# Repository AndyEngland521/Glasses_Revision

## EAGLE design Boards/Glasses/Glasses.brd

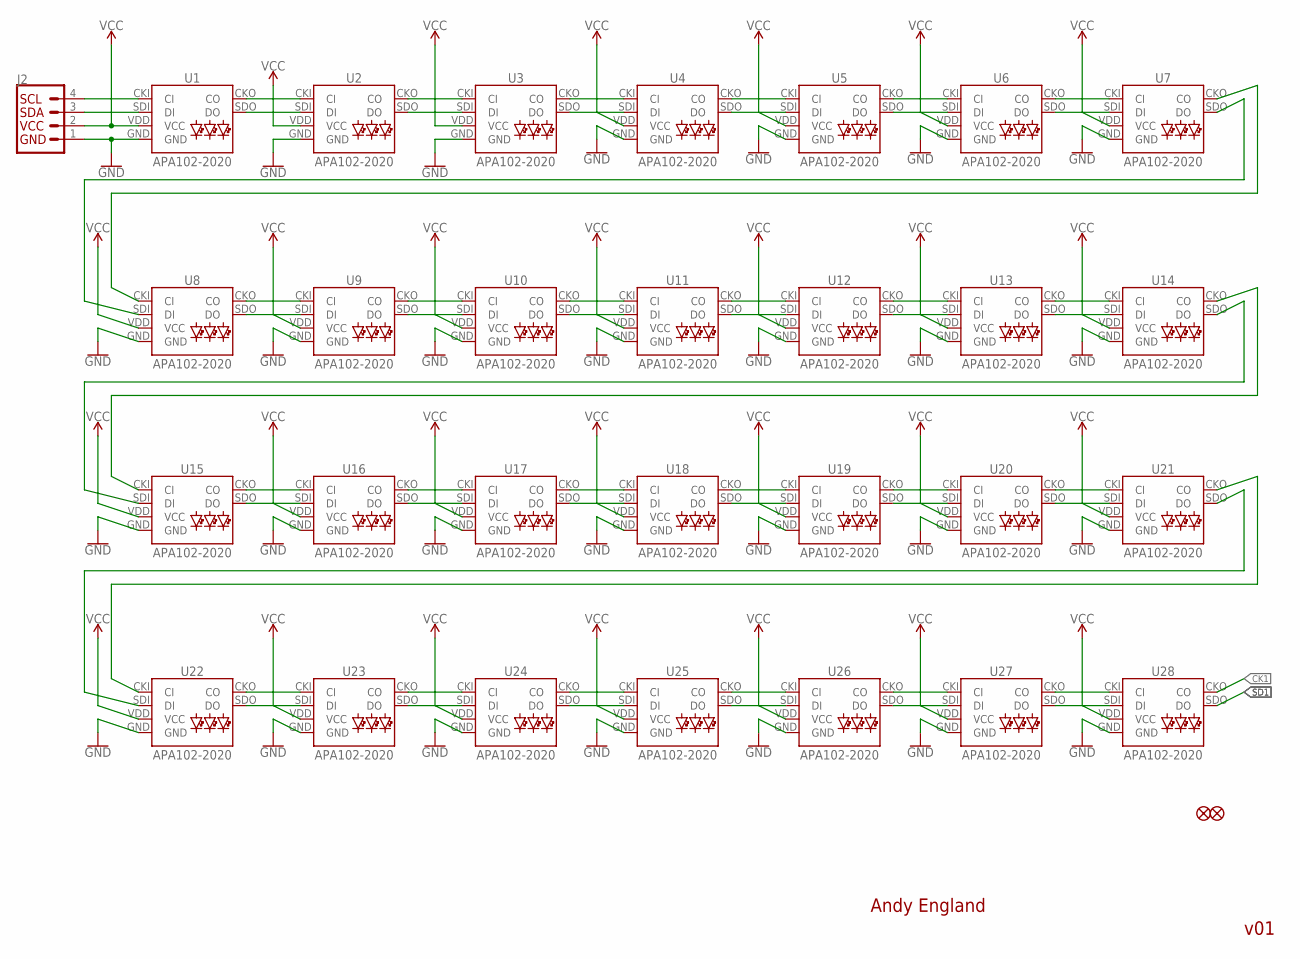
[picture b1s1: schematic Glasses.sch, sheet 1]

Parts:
FD1, FD2: FIDUCIALUFIDUCIAL; FIDUCIAL-MICRO
J2: QWIIC_CONNECTORJS-1MM; 1X04_1MM_RA
U1, U2, U3, U4, U5, U6, U7, U8, U9, U10, U11, U12, U13, U14, U15, U16, U17, U18, U19, U20, U21, U22, U23, U24, U25, U26, U27, U28: APA102-2020

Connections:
CK1: U28.CKO (CO); also elsewhere on the board
GND: J2.1, U1.GND, U2.GND, U3.GND, U4.GND, U5.GND, U6.GND, U7.GND, U8.GND, U9.GND, U10.GND, U11.GND, U12.GND, U13.GND, U14.GND, U15.GND, U16.GND, U17.GND, U18.GND, U19.GND, U20.GND, U21.GND, U22.GND, U23.GND, U24.GND, U25.GND, U26.GND, U27.GND, U28.GND; also elsewhere on the board
unnamed: U1.SDO (DO), U2.SDI (DI)
unnamed: U1.CKO (CO), U2.CKI (CI)
unnamed: U2.CKO (CO), U3.CKI (CI)
unnamed: U2.SDO (DO), U3.SDI (DI)
unnamed: U3.SDO (DO), U4.SDI (DI)
unnamed: U3.CKO (CO), U4.CKI (CI)
unnamed: U4.CKO (CO), U5.CKI (CI)
unnamed: U4.SDO (DO), U5.SDI (DI)
unnamed: U5.CKO (CO), U6.CKI (CI)
unnamed: U5.SDO (DO), U6.SDI (DI)
unnamed: U6.CKO (CO), U7.CKI (CI)
unnamed: U6.SDO (DO), U7.SDI (DI)
unnamed: U8.SDO (DO), U9.SDI (DI)
unnamed: U8.CKO (CO), U9.CKI (CI)
unnamed: U9.CKO (CO), U10.CKI (CI)
unnamed: U9.SDO (DO), U10.SDI (DI)
unnamed: U10.SDO (DO), U11.SDI (DI)
unnamed: U10.CKO (CO), U11.CKI (CI)
unnamed: U11.CKO (CO), U12.CKI (CI)
unnamed: U11.SDO (DO), U12.SDI (DI)
unnamed: U12.CKO (CO), U13.CKI (CI)
unnamed: U12.SDO (DO), U13.SDI (DI)
unnamed: U13.CKO (CO), U14.CKI (CI)
unnamed: U13.SDO (DO), U14.SDI (DI)
unnamed: U7.SDO (DO), U8.SDI (DI)
unnamed: U7.CKO (CO), U8.CKI (CI)
unnamed: U15.SDO (DO), U16.SDI (DI)
unnamed: U15.CKO (CO), U16.CKI (CI)
unnamed: U16.CKO (CO), U17.CKI (CI)
unnamed: U16.SDO (DO), U17.SDI (DI)
unnamed: U17.SDO (DO), U18.SDI (DI)
unnamed: U17.CKO (CO), U18.CKI (CI)
unnamed: U18.CKO (CO), U19.CKI (CI)
unnamed: U18.SDO (DO), U19.SDI (DI)
unnamed: U19.CKO (CO), U20.CKI (CI)
unnamed: U19.SDO (DO), U20.SDI (DI)
unnamed: U20.CKO (CO), U21.CKI (CI)
unnamed: U20.SDO (DO), U21.SDI (DI)
unnamed: U22.SDO (DO), U23.SDI (DI)
unnamed: U22.CKO (CO), U23.CKI (CI)
unnamed: U23.CKO (CO), U24.CKI (CI)
unnamed: U23.SDO (DO), U24.SDI (DI)
unnamed: U24.SDO (DO), U25.SDI (DI)
unnamed: U24.CKO (CO), U25.CKI (CI)
unnamed: U25.CKO (CO), U26.CKI (CI)
unnamed: U25.SDO (DO), U26.SDI (DI)
unnamed: U26.CKO (CO), U27.CKI (CI)
unnamed: U26.SDO (DO), U27.SDI (DI)
unnamed: U27.CKO (CO), U28.CKI (CI)
unnamed: U27.SDO (DO), U28.SDI (DI)
unnamed: U21.SDO (DO), U22.SDI (DI)
unnamed: U21.CKO (CO), U22.CKI (CI)
unnamed: U14.SDO (DO), U15.SDI (DI)
unnamed: U14.CKO (CO), U15.CKI (CI)
unnamed: J2.3, U1.SDI (DI)
unnamed: J2.4, U1.CKI (CI)
SD1: U28.SDO (DO); also elsewhere on the board
VCC: J2.2, U1.VDD (VCC), U2.VDD (VCC), U3.VDD (VCC), U4.VDD (VCC), U5.VDD (VCC), U6.VDD (VCC), U7.VDD (VCC), U8.VDD (VCC), U9.VDD (VCC), U10.VDD (VCC), U11.VDD (VCC), U12.VDD (VCC), U13.VDD (VCC), U14.VDD (VCC), U15.VDD (VCC), U16.VDD (VCC), U17.VDD (VCC), U18.VDD (VCC), U19.VDD (VCC), U20.VDD (VCC), U21.VDD (VCC), U22.VDD (VCC), U23.VDD (VCC), U24.VDD (VCC), U25.VDD (VCC), U26.VDD (VCC), U27.VDD (VCC), U28.VDD (VCC); also elsewhere on the board

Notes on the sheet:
Andy England
v01

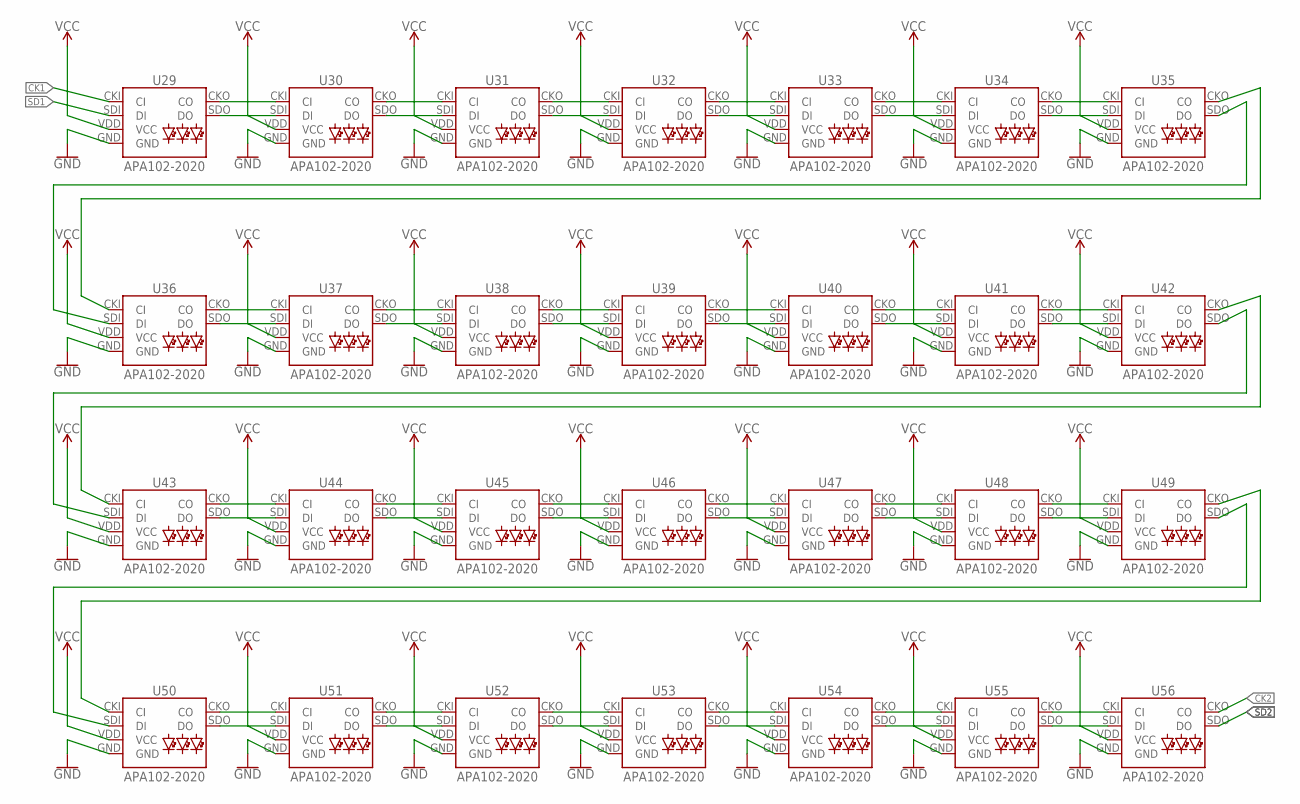
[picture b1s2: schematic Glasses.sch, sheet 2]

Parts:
U29, U30, U31, U32, U33, U34, U35, U36, U37, U38, U39, U40, U41, U42, U43, U44, U45, U46, U47, U48, U49, U50, U51, U52, U53, U54, U55, U56: APA102-2020

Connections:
CK1: U29.CKI (CI); also elsewhere on the board
CK2: U56.CKO (CO); also elsewhere on the board
GND: U29.GND, U30.GND, U31.GND, U32.GND, U33.GND, U34.GND, U35.GND, U36.GND, U37.GND, U38.GND, U39.GND, U40.GND, U41.GND, U42.GND, U43.GND, U44.GND, U45.GND, U46.GND, U47.GND, U48.GND, U49.GND, U50.GND, U51.GND, U52.GND, U53.GND, U54.GND, U55.GND, U56.GND; also elsewhere on the board
unnamed: U29.SDO (DO), U30.SDI (DI)
unnamed: U29.CKO (CO), U30.CKI (CI)
unnamed: U30.CKO (CO), U31.CKI (CI)
unnamed: U30.SDO (DO), U31.SDI (DI)
unnamed: U31.SDO (DO), U32.SDI (DI)
unnamed: U31.CKO (CO), U32.CKI (CI)
unnamed: U32.CKO (CO), U33.CKI (CI)
unnamed: U32.SDO (DO), U33.SDI (DI)
unnamed: U33.CKO (CO), U34.CKI (CI)
unnamed: U33.SDO (DO), U34.SDI (DI)
unnamed: U34.CKO (CO), U35.CKI (CI)
unnamed: U34.SDO (DO), U35.SDI (DI)
unnamed: U36.SDO (DO), U37.SDI (DI)
unnamed: U36.CKO (CO), U37.CKI (CI)
unnamed: U37.CKO (CO), U38.CKI (CI)
unnamed: U37.SDO (DO), U38.SDI (DI)
unnamed: U38.SDO (DO), U39.SDI (DI)
unnamed: U38.CKO (CO), U39.CKI (CI)
unnamed: U39.CKO (CO), U40.CKI (CI)
unnamed: U39.SDO (DO), U40.SDI (DI)
unnamed: U40.CKO (CO), U41.CKI (CI)
unnamed: U40.SDO (DO), U41.SDI (DI)
unnamed: U41.CKO (CO), U42.CKI (CI)
unnamed: U41.SDO (DO), U42.SDI (DI)
unnamed: U35.SDO (DO), U36.SDI (DI)
unnamed: U35.CKO (CO), U36.CKI (CI)
unnamed: U43.SDO (DO), U44.SDI (DI)
unnamed: U43.CKO (CO), U44.CKI (CI)
unnamed: U44.CKO (CO), U45.CKI (CI)
unnamed: U44.SDO (DO), U45.SDI (DI)
unnamed: U45.SDO (DO), U46.SDI (DI)
unnamed: U45.CKO (CO), U46.CKI (CI)
unnamed: U46.CKO (CO), U47.CKI (CI)
unnamed: U46.SDO (DO), U47.SDI (DI)
unnamed: U47.CKO (CO), U48.CKI (CI)
unnamed: U47.SDO (DO), U48.SDI (DI)
unnamed: U48.CKO (CO), U49.CKI (CI)
unnamed: U48.SDO (DO), U49.SDI (DI)
unnamed: U50.SDO (DO), U51.SDI (DI)
unnamed: U50.CKO (CO), U51.CKI (CI)
unnamed: U51.CKO (CO), U52.CKI (CI)
unnamed: U51.SDO (DO), U52.SDI (DI)
unnamed: U52.SDO (DO), U53.SDI (DI)
unnamed: U52.CKO (CO), U53.CKI (CI)
unnamed: U53.CKO (CO), U54.CKI (CI)
unnamed: U53.SDO (DO), U54.SDI (DI)
unnamed: U54.CKO (CO), U55.CKI (CI)
unnamed: U54.SDO (DO), U55.SDI (DI)
unnamed: U55.CKO (CO), U56.CKI (CI)
unnamed: U55.SDO (DO), U56.SDI (DI)
unnamed: U49.SDO (DO), U50.SDI (DI)
unnamed: U49.CKO (CO), U50.CKI (CI)
unnamed: U42.SDO (DO), U43.SDI (DI)
unnamed: U42.CKO (CO), U43.CKI (CI)
SD1: U29.SDI (DI); also elsewhere on the board
SD2: U56.SDO (DO); also elsewhere on the board
VCC: U29.VDD (VCC), U30.VDD (VCC), U31.VDD (VCC), U32.VDD (VCC), U33.VDD (VCC), U34.VDD (VCC), U35.VDD (VCC), U36.VDD (VCC), U37.VDD (VCC), U38.VDD (VCC), U39.VDD (VCC), U40.VDD (VCC), U41.VDD (VCC), U42.VDD (VCC), U43.VDD (VCC), U44.VDD (VCC), U45.VDD (VCC), U46.VDD (VCC), U47.VDD (VCC), U48.VDD (VCC), U49.VDD (VCC), U50.VDD (VCC), U51.VDD (VCC), U52.VDD (VCC), U53.VDD (VCC), U54.VDD (VCC), U55.VDD (VCC), U56.VDD (VCC); also elsewhere on the board

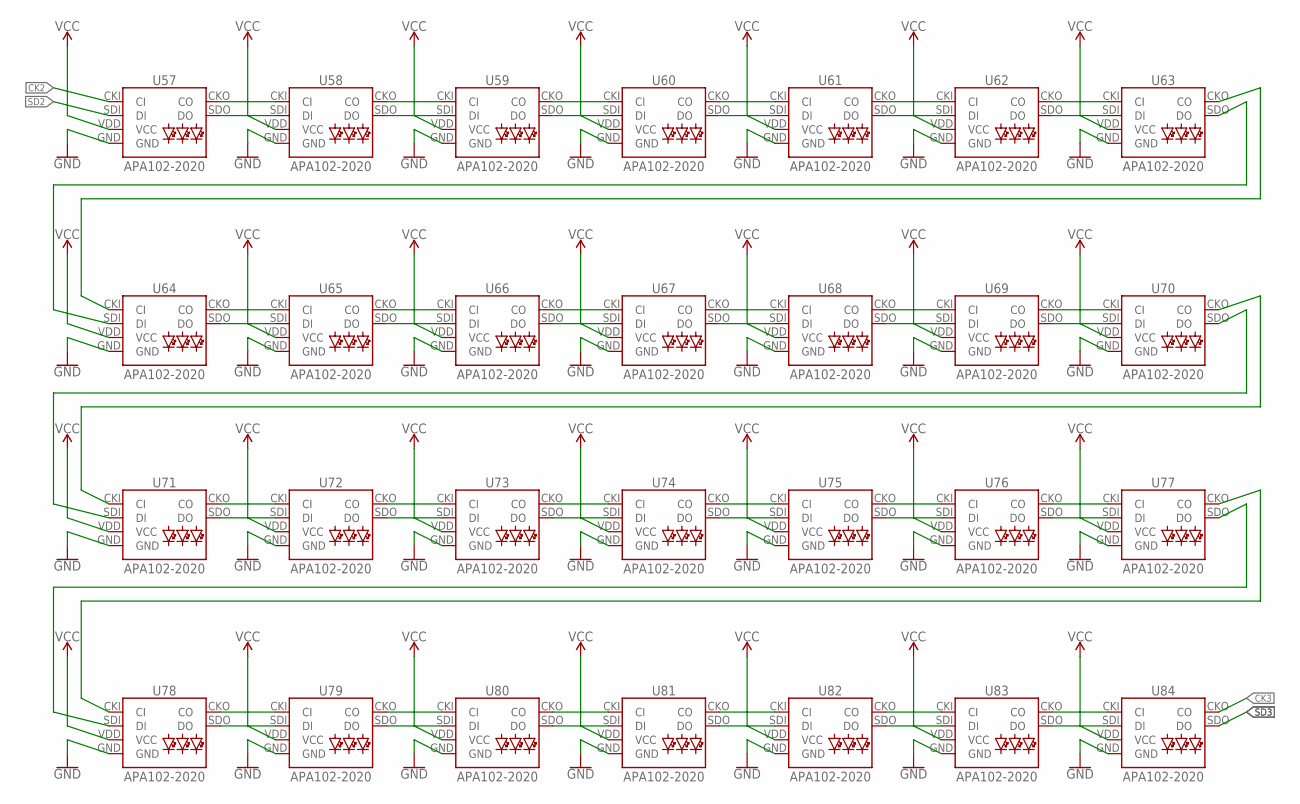
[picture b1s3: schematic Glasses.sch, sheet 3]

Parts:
U57, U58, U59, U60, U61, U62, U63, U64, U65, U66, U67, U68, U69, U70, U71, U72, U73, U74, U75, U76, U77, U78, U79, U80, U81, U82, U83, U84: APA102-2020

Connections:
CK2: U57.CKI (CI); also elsewhere on the board
CK3: U84.CKO (CO); also elsewhere on the board
GND: U57.GND, U58.GND, U59.GND, U60.GND, U61.GND, U62.GND, U63.GND, U64.GND, U65.GND, U66.GND, U67.GND, U68.GND, U69.GND, U70.GND, U71.GND, U72.GND, U73.GND, U74.GND, U75.GND, U76.GND, U77.GND, U78.GND, U79.GND, U80.GND, U81.GND, U82.GND, U83.GND, U84.GND; also elsewhere on the board
unnamed: U57.SDO (DO), U58.SDI (DI)
unnamed: U57.CKO (CO), U58.CKI (CI)
unnamed: U58.CKO (CO), U59.CKI (CI)
unnamed: U58.SDO (DO), U59.SDI (DI)
unnamed: U59.SDO (DO), U60.SDI (DI)
unnamed: U59.CKO (CO), U60.CKI (CI)
unnamed: U60.CKO (CO), U61.CKI (CI)
unnamed: U60.SDO (DO), U61.SDI (DI)
unnamed: U61.CKO (CO), U62.CKI (CI)
unnamed: U61.SDO (DO), U62.SDI (DI)
unnamed: U62.CKO (CO), U63.CKI (CI)
unnamed: U62.SDO (DO), U63.SDI (DI)
unnamed: U64.SDO (DO), U65.SDI (DI)
unnamed: U64.CKO (CO), U65.CKI (CI)
unnamed: U65.CKO (CO), U66.CKI (CI)
unnamed: U65.SDO (DO), U66.SDI (DI)
unnamed: U66.SDO (DO), U67.SDI (DI)
unnamed: U66.CKO (CO), U67.CKI (CI)
unnamed: U67.CKO (CO), U68.CKI (CI)
unnamed: U67.SDO (DO), U68.SDI (DI)
unnamed: U68.CKO (CO), U69.CKI (CI)
unnamed: U68.SDO (DO), U69.SDI (DI)
unnamed: U69.CKO (CO), U70.CKI (CI)
unnamed: U69.SDO (DO), U70.SDI (DI)
unnamed: U63.SDO (DO), U64.SDI (DI)
unnamed: U63.CKO (CO), U64.CKI (CI)
unnamed: U71.SDO (DO), U72.SDI (DI)
unnamed: U71.CKO (CO), U72.CKI (CI)
unnamed: U72.CKO (CO), U73.CKI (CI)
unnamed: U72.SDO (DO), U73.SDI (DI)
unnamed: U73.SDO (DO), U74.SDI (DI)
unnamed: U73.CKO (CO), U74.CKI (CI)
unnamed: U74.CKO (CO), U75.CKI (CI)
unnamed: U74.SDO (DO), U75.SDI (DI)
unnamed: U75.CKO (CO), U76.CKI (CI)
unnamed: U75.SDO (DO), U76.SDI (DI)
unnamed: U76.CKO (CO), U77.CKI (CI)
unnamed: U76.SDO (DO), U77.SDI (DI)
unnamed: U78.SDO (DO), U79.SDI (DI)
unnamed: U78.CKO (CO), U79.CKI (CI)
unnamed: U79.CKO (CO), U80.CKI (CI)
unnamed: U79.SDO (DO), U80.SDI (DI)
unnamed: U80.SDO (DO), U81.SDI (DI)
unnamed: U80.CKO (CO), U81.CKI (CI)
unnamed: U81.CKO (CO), U82.CKI (CI)
unnamed: U81.SDO (DO), U82.SDI (DI)
unnamed: U82.CKO (CO), U83.CKI (CI)
unnamed: U82.SDO (DO), U83.SDI (DI)
unnamed: U83.CKO (CO), U84.CKI (CI)
unnamed: U83.SDO (DO), U84.SDI (DI)
unnamed: U77.SDO (DO), U78.SDI (DI)
unnamed: U77.CKO (CO), U78.CKI (CI)
unnamed: U70.SDO (DO), U71.SDI (DI)
unnamed: U70.CKO (CO), U71.CKI (CI)
SD2: U57.SDI (DI); also elsewhere on the board
SD3: U84.SDO (DO); also elsewhere on the board
VCC: U57.VDD (VCC), U58.VDD (VCC), U59.VDD (VCC), U60.VDD (VCC), U61.VDD (VCC), U62.VDD (VCC), U63.VDD (VCC), U64.VDD (VCC), U65.VDD (VCC), U66.VDD (VCC), U67.VDD (VCC), U68.VDD (VCC), U69.VDD (VCC), U70.VDD (VCC), U71.VDD (VCC), U72.VDD (VCC), U73.VDD (VCC), U74.VDD (VCC), U75.VDD (VCC), U76.VDD (VCC), U77.VDD (VCC), U78.VDD (VCC), U79.VDD (VCC), U80.VDD (VCC), U81.VDD (VCC), U82.VDD (VCC), U83.VDD (VCC), U84.VDD (VCC); also elsewhere on the board

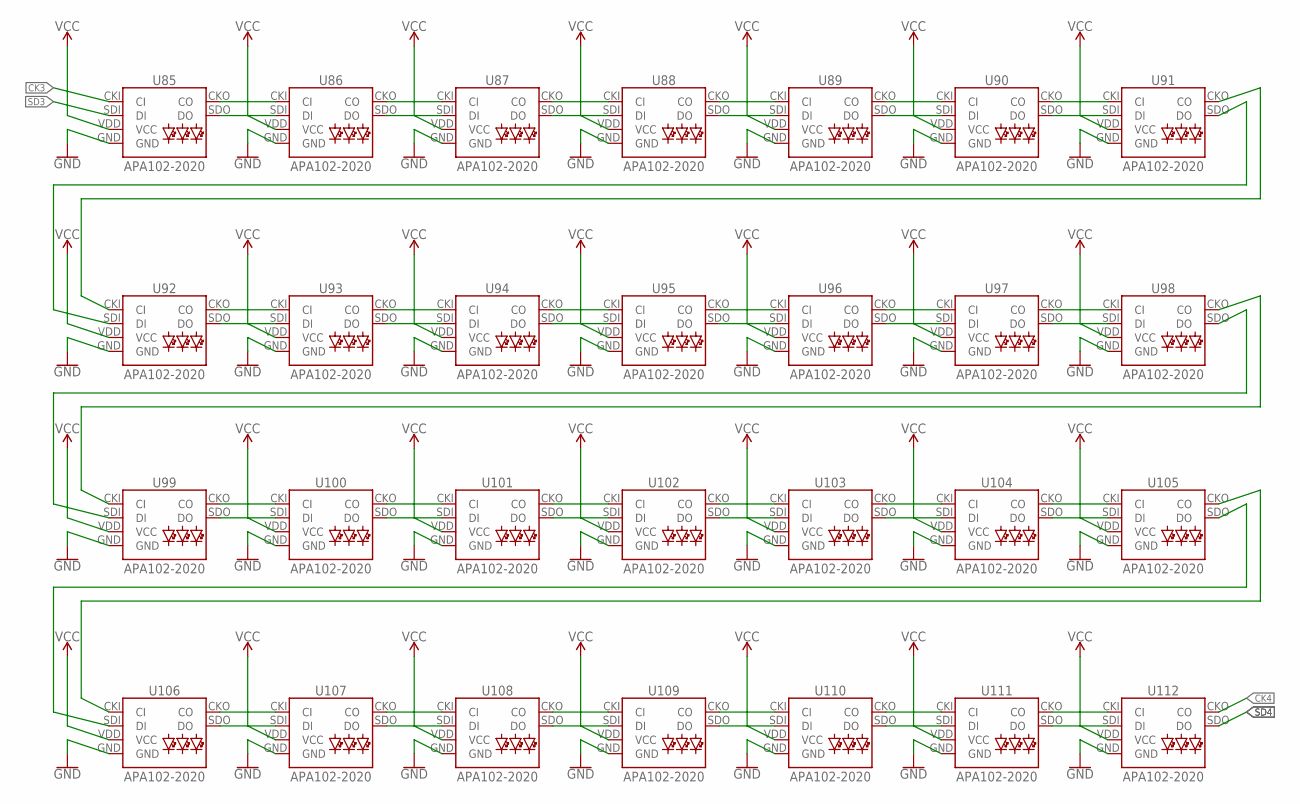
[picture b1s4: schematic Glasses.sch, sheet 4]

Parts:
U85, U86, U87, U88, U89, U90, U91, U92, U93, U94, U95, U96, U97, U98, U99, U100, U101, U102, U103, U104, U105, U106, U107, U108, U109, U110, U111, U112: APA102-2020

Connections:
CK3: U85.CKI (CI); also elsewhere on the board
CK4: U112.CKO (CO); also elsewhere on the board
GND: U85.GND, U86.GND, U87.GND, U88.GND, U89.GND, U90.GND, U91.GND, U92.GND, U93.GND, U94.GND, U95.GND, U96.GND, U97.GND, U98.GND, U99.GND, U100.GND, U101.GND, U102.GND, U103.GND, U104.GND, U105.GND, U106.GND, U107.GND, U108.GND, U109.GND, U110.GND, U111.GND, U112.GND; also elsewhere on the board
unnamed: U85.SDO (DO), U86.SDI (DI)
unnamed: U85.CKO (CO), U86.CKI (CI)
unnamed: U86.CKO (CO), U87.CKI (CI)
unnamed: U86.SDO (DO), U87.SDI (DI)
unnamed: U87.SDO (DO), U88.SDI (DI)
unnamed: U87.CKO (CO), U88.CKI (CI)
unnamed: U88.CKO (CO), U89.CKI (CI)
unnamed: U88.SDO (DO), U89.SDI (DI)
unnamed: U89.CKO (CO), U90.CKI (CI)
unnamed: U89.SDO (DO), U90.SDI (DI)
unnamed: U90.CKO (CO), U91.CKI (CI)
unnamed: U90.SDO (DO), U91.SDI (DI)
unnamed: U92.SDO (DO), U93.SDI (DI)
unnamed: U92.CKO (CO), U93.CKI (CI)
unnamed: U93.CKO (CO), U94.CKI (CI)
unnamed: U93.SDO (DO), U94.SDI (DI)
unnamed: U94.SDO (DO), U95.SDI (DI)
unnamed: U94.CKO (CO), U95.CKI (CI)
unnamed: U95.SDO (DO), U96.SDI (DI)
unnamed: U95.CKO (CO), U96.CKI (CI)
unnamed: U96.CKO (CO), U97.CKI (CI)
unnamed: U96.SDO (DO), U97.SDI (DI)
unnamed: U97.CKO (CO), U98.CKI (CI)
unnamed: U97.SDO (DO), U98.SDI (DI)
unnamed: U91.SDO (DO), U92.SDI (DI)
unnamed: U91.CKO (CO), U92.CKI (CI)
unnamed: U99.SDO (DO), U100.SDI (DI)
unnamed: U99.CKO (CO), U100.CKI (CI)
unnamed: U100.CKO (CO), U101.CKI (CI)
unnamed: U100.SDO (DO), U101.SDI (DI)
unnamed: U101.SDO (DO), U102.SDI (DI)
unnamed: U101.CKO (CO), U102.CKI (CI)
unnamed: U102.CKO (CO), U103.CKI (CI)
unnamed: U102.SDO (DO), U103.SDI (DI)
unnamed: U103.CKO (CO), U104.CKI (CI)
unnamed: U103.SDO (DO), U104.SDI (DI)
unnamed: U104.CKO (CO), U105.CKI (CI)
unnamed: U104.SDO (DO), U105.SDI (DI)
unnamed: U106.SDO (DO), U107.SDI (DI)
unnamed: U106.CKO (CO), U107.CKI (CI)
unnamed: U107.CKO (CO), U108.CKI (CI)
unnamed: U107.SDO (DO), U108.SDI (DI)
unnamed: U108.SDO (DO), U109.SDI (DI)
unnamed: U108.CKO (CO), U109.CKI (CI)
unnamed: U109.CKO (CO), U110.CKI (CI)
unnamed: U109.SDO (DO), U110.SDI (DI)
unnamed: U110.CKO (CO), U111.CKI (CI)
unnamed: U110.SDO (DO), U111.SDI (DI)
unnamed: U111.CKO (CO), U112.CKI (CI)
unnamed: U111.SDO (DO), U112.SDI (DI)
unnamed: U105.SDO (DO), U106.SDI (DI)
unnamed: U105.CKO (CO), U106.CKI (CI)
unnamed: U98.SDO (DO), U99.SDI (DI)
unnamed: U98.CKO (CO), U99.CKI (CI)
SD3: U85.SDI (DI); also elsewhere on the board
SD4: U112.SDO (DO); also elsewhere on the board
VCC: U85.VDD (VCC), U86.VDD (VCC), U87.VDD (VCC), U88.VDD (VCC), U89.VDD (VCC), U90.VDD (VCC), U91.VDD (VCC), U92.VDD (VCC), U93.VDD (VCC), U94.VDD (VCC), U95.VDD (VCC), U96.VDD (VCC), U97.VDD (VCC), U98.VDD (VCC), U99.VDD (VCC), U100.VDD (VCC), U101.VDD (VCC), U102.VDD (VCC), U103.VDD (VCC), U104.VDD (VCC), U105.VDD (VCC), U106.VDD (VCC), U107.VDD (VCC), U108.VDD (VCC), U109.VDD (VCC), U110.VDD (VCC), U111.VDD (VCC), U112.VDD (VCC); also elsewhere on the board

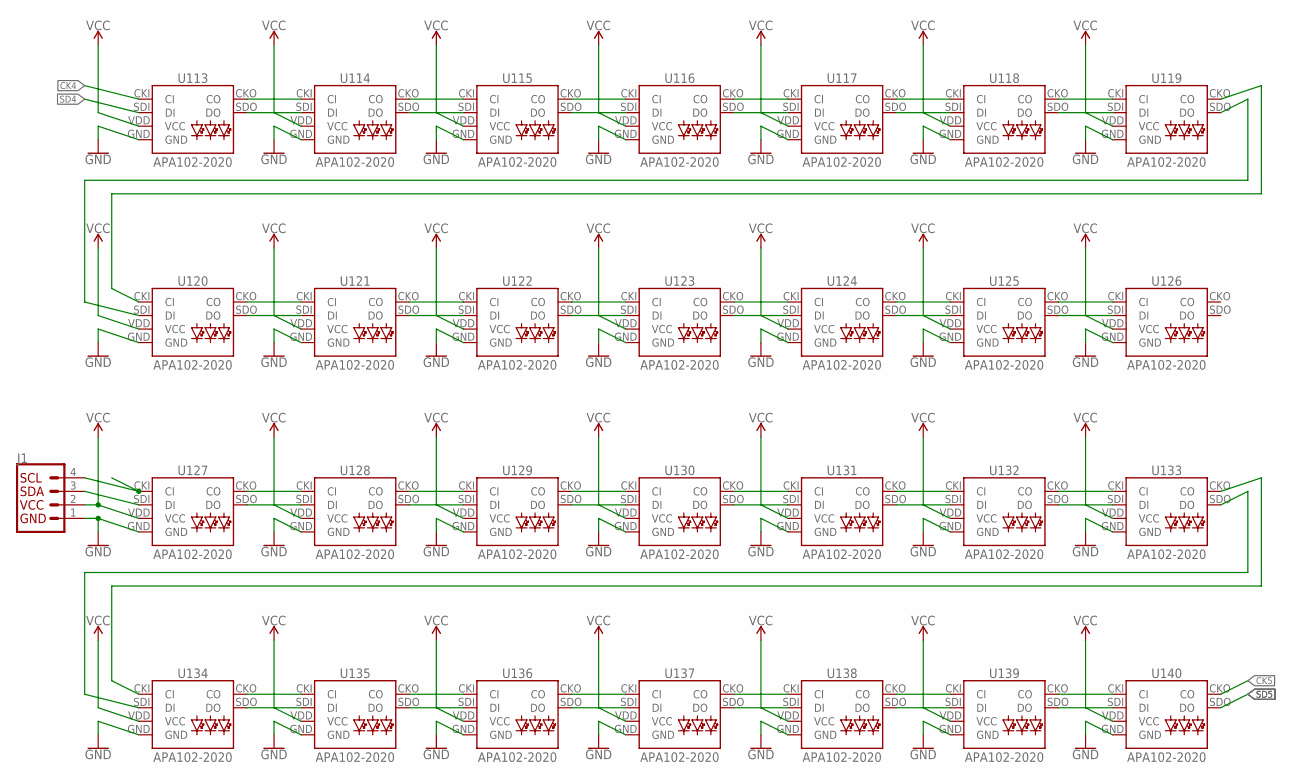
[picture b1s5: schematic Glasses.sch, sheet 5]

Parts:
J1: QWIIC_CONNECTORJS-1MM; 1X04_1MM_RA
U113, U114, U115, U116, U117, U118, U119, U120, U121, U122, U123, U124, U125, U126, U127, U128, U129, U130, U131, U132, U133, U134, U135, U136, U137, U138, U139, U140: APA102-2020

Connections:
CK4: U113.CKI (CI); also elsewhere on the board
CK5: U140.CKO (CO); also elsewhere on the board
GND: J1.1, U113.GND, U114.GND, U115.GND, U116.GND, U117.GND, U118.GND, U119.GND, U120.GND, U121.GND, U122.GND, U123.GND, U124.GND, U125.GND, U126.GND, U127.GND, U128.GND, U129.GND, U130.GND, U131.GND, U132.GND, U133.GND, U134.GND, U135.GND, U136.GND, U137.GND, U138.GND, U139.GND, U140.GND; also elsewhere on the board
unnamed: U113.SDO (DO), U114.SDI (DI)
unnamed: U113.CKO (CO), U114.CKI (CI)
unnamed: U114.CKO (CO), U115.CKI (CI)
unnamed: U114.SDO (DO), U115.SDI (DI)
unnamed: U115.SDO (DO), U116.SDI (DI)
unnamed: U115.CKO (CO), U116.CKI (CI)
unnamed: U116.CKO (CO), U117.CKI (CI)
unnamed: U116.SDO (DO), U117.SDI (DI)
unnamed: U117.CKO (CO), U118.CKI (CI)
unnamed: U117.SDO (DO), U118.SDI (DI)
unnamed: U118.CKO (CO), U119.CKI (CI)
unnamed: U118.SDO (DO), U119.SDI (DI)
unnamed: U120.SDO (DO), U121.SDI (DI)
unnamed: U120.CKO (CO), U121.CKI (CI)
unnamed: U121.CKO (CO), U122.CKI (CI)
unnamed: U121.SDO (DO), U122.SDI (DI)
unnamed: U122.SDO (DO), U123.SDI (DI)
unnamed: U122.CKO (CO), U123.CKI (CI)
unnamed: U123.CKO (CO), U124.CKI (CI)
unnamed: U123.SDO (DO), U124.SDI (DI)
unnamed: U124.CKO (CO), U125.CKI (CI)
unnamed: U124.SDO (DO), U125.SDI (DI)
unnamed: U125.CKO (CO), U126.CKI (CI)
unnamed: U125.SDO (DO), U126.SDI (DI)
unnamed: U119.SDO (DO), U120.SDI (DI)
unnamed: U119.CKO (CO), U120.CKI (CI)
unnamed: U127.SDO (DO), U128.SDI (DI)
unnamed: U127.CKO (CO), U128.CKI (CI)
unnamed: U128.CKO (CO), U129.CKI (CI)
unnamed: U128.SDO (DO), U129.SDI (DI)
unnamed: U129.SDO (DO), U130.SDI (DI)
unnamed: U129.CKO (CO), U130.CKI (CI)
unnamed: U130.CKO (CO), U131.CKI (CI)
unnamed: U130.SDO (DO), U131.SDI (DI)
unnamed: U131.CKO (CO), U132.CKI (CI)
unnamed: U131.SDO (DO), U132.SDI (DI)
unnamed: U132.CKO (CO), U133.CKI (CI)
unnamed: U132.SDO (DO), U133.SDI (DI)
unnamed: U134.SDO (DO), U135.SDI (DI)
unnamed: U134.CKO (CO), U135.CKI (CI)
unnamed: U135.CKO (CO), U136.CKI (CI)
unnamed: U135.SDO (DO), U136.SDI (DI)
unnamed: U136.SDO (DO), U137.SDI (DI)
unnamed: U136.CKO (CO), U137.CKI (CI)
unnamed: U137.CKO (CO), U138.CKI (CI)
unnamed: U137.SDO (DO), U138.SDI (DI)
unnamed: U138.CKO (CO), U139.CKI (CI)
unnamed: U138.SDO (DO), U139.SDI (DI)
unnamed: U139.CKO (CO), U140.CKI (CI)
unnamed: U139.SDO (DO), U140.SDI (DI)
unnamed: U133.SDO (DO), U134.SDI (DI)
unnamed: U133.CKO (CO), U134.CKI (CI)
unnamed: J1.3, U127.SDI (DI)
unnamed: J1.4, U127.CKI (CI)
SD4: U113.SDI (DI); also elsewhere on the board
SD5: U140.SDO (DO); also elsewhere on the board
VCC: J1.2, U113.VDD (VCC), U114.VDD (VCC), U115.VDD (VCC), U116.VDD (VCC), U117.VDD (VCC), U118.VDD (VCC), U119.VDD (VCC), U120.VDD (VCC), U121.VDD (VCC), U122.VDD (VCC), U123.VDD (VCC), U124.VDD (VCC), U125.VDD (VCC), U126.VDD (VCC), U127.VDD (VCC), U128.VDD (VCC), U129.VDD (VCC), U130.VDD (VCC), U131.VDD (VCC), U132.VDD (VCC), U133.VDD (VCC), U134.VDD (VCC), U135.VDD (VCC), U136.VDD (VCC), U137.VDD (VCC), U138.VDD (VCC), U139.VDD (VCC), U140.VDD (VCC); also elsewhere on the board

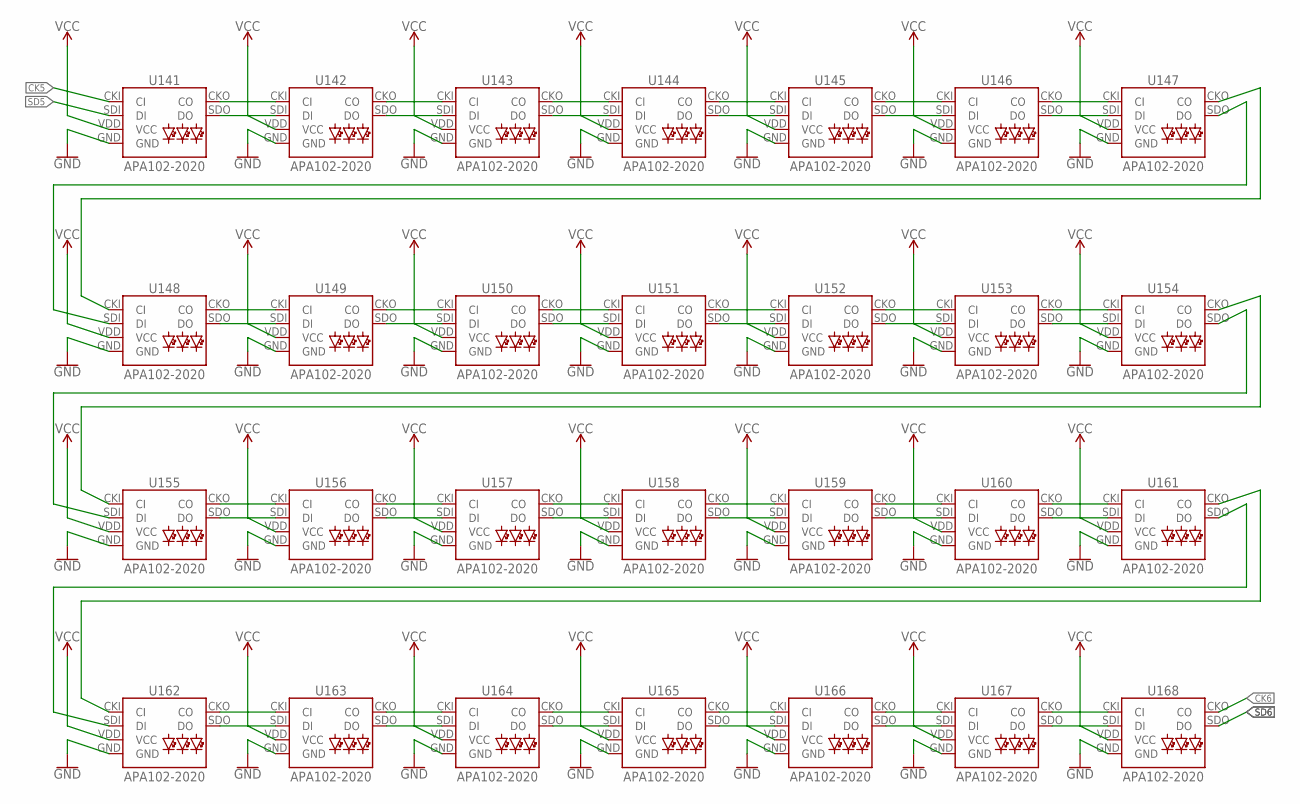
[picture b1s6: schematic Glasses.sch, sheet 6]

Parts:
U141, U142, U143, U144, U145, U146, U147, U148, U149, U150, U151, U152, U153, U154, U155, U156, U157, U158, U159, U160, U161, U162, U163, U164, U165, U166, U167, U168: APA102-2020

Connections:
CK5: U141.CKI (CI); also elsewhere on the board
CK6: U168.CKO (CO); also elsewhere on the board
GND: U141.GND, U142.GND, U143.GND, U144.GND, U145.GND, U146.GND, U147.GND, U148.GND, U149.GND, U150.GND, U151.GND, U152.GND, U153.GND, U154.GND, U155.GND, U156.GND, U157.GND, U158.GND, U159.GND, U160.GND, U161.GND, U162.GND, U163.GND, U164.GND, U165.GND, U166.GND, U167.GND, U168.GND; also elsewhere on the board
unnamed: U141.SDO (DO), U142.SDI (DI)
unnamed: U141.CKO (CO), U142.CKI (CI)
unnamed: U142.CKO (CO), U143.CKI (CI)
unnamed: U142.SDO (DO), U143.SDI (DI)
unnamed: U143.SDO (DO), U144.SDI (DI)
unnamed: U143.CKO (CO), U144.CKI (CI)
unnamed: U144.CKO (CO), U145.CKI (CI)
unnamed: U144.SDO (DO), U145.SDI (DI)
unnamed: U145.CKO (CO), U146.CKI (CI)
unnamed: U145.SDO (DO), U146.SDI (DI)
unnamed: U146.CKO (CO), U147.CKI (CI)
unnamed: U146.SDO (DO), U147.SDI (DI)
unnamed: U148.SDO (DO), U149.SDI (DI)
unnamed: U148.CKO (CO), U149.CKI (CI)
unnamed: U149.CKO (CO), U150.CKI (CI)
unnamed: U149.SDO (DO), U150.SDI (DI)
unnamed: U150.SDO (DO), U151.SDI (DI)
unnamed: U150.CKO (CO), U151.CKI (CI)
unnamed: U151.CKO (CO), U152.CKI (CI)
unnamed: U151.SDO (DO), U152.SDI (DI)
unnamed: U152.CKO (CO), U153.CKI (CI)
unnamed: U152.SDO (DO), U153.SDI (DI)
unnamed: U153.CKO (CO), U154.CKI (CI)
unnamed: U153.SDO (DO), U154.SDI (DI)
unnamed: U147.SDO (DO), U148.SDI (DI)
unnamed: U147.CKO (CO), U148.CKI (CI)
unnamed: U155.SDO (DO), U156.SDI (DI)
unnamed: U155.CKO (CO), U156.CKI (CI)
unnamed: U156.CKO (CO), U157.CKI (CI)
unnamed: U156.SDO (DO), U157.SDI (DI)
unnamed: U157.SDO (DO), U158.SDI (DI)
unnamed: U157.CKO (CO), U158.CKI (CI)
unnamed: U158.CKO (CO), U159.CKI (CI)
unnamed: U158.SDO (DO), U159.SDI (DI)
unnamed: U159.CKO (CO), U160.CKI (CI)
unnamed: U159.SDO (DO), U160.SDI (DI)
unnamed: U160.CKO (CO), U161.CKI (CI)
unnamed: U160.SDO (DO), U161.SDI (DI)
unnamed: U162.SDO (DO), U163.SDI (DI)
unnamed: U162.CKO (CO), U163.CKI (CI)
unnamed: U163.CKO (CO), U164.CKI (CI)
unnamed: U163.SDO (DO), U164.SDI (DI)
unnamed: U164.SDO (DO), U165.SDI (DI)
unnamed: U164.CKO (CO), U165.CKI (CI)
unnamed: U165.CKO (CO), U166.CKI (CI)
unnamed: U165.SDO (DO), U166.SDI (DI)
unnamed: U166.CKO (CO), U167.CKI (CI)
unnamed: U166.SDO (DO), U167.SDI (DI)
unnamed: U167.CKO (CO), U168.CKI (CI)
unnamed: U167.SDO (DO), U168.SDI (DI)
unnamed: U161.SDO (DO), U162.SDI (DI)
unnamed: U161.CKO (CO), U162.CKI (CI)
unnamed: U154.SDO (DO), U155.SDI (DI)
unnamed: U154.CKO (CO), U155.CKI (CI)
SD5: U141.SDI (DI); also elsewhere on the board
SD6: U168.SDO (DO); also elsewhere on the board
VCC: U141.VDD (VCC), U142.VDD (VCC), U143.VDD (VCC), U144.VDD (VCC), U145.VDD (VCC), U146.VDD (VCC), U147.VDD (VCC), U148.VDD (VCC), U149.VDD (VCC), U150.VDD (VCC), U151.VDD (VCC), U152.VDD (VCC), U153.VDD (VCC), U154.VDD (VCC), U155.VDD (VCC), U156.VDD (VCC), U157.VDD (VCC), U158.VDD (VCC), U159.VDD (VCC), U160.VDD (VCC), U161.VDD (VCC), U162.VDD (VCC), U163.VDD (VCC), U164.VDD (VCC), U165.VDD (VCC), U166.VDD (VCC), U167.VDD (VCC), U168.VDD (VCC); also elsewhere on the board

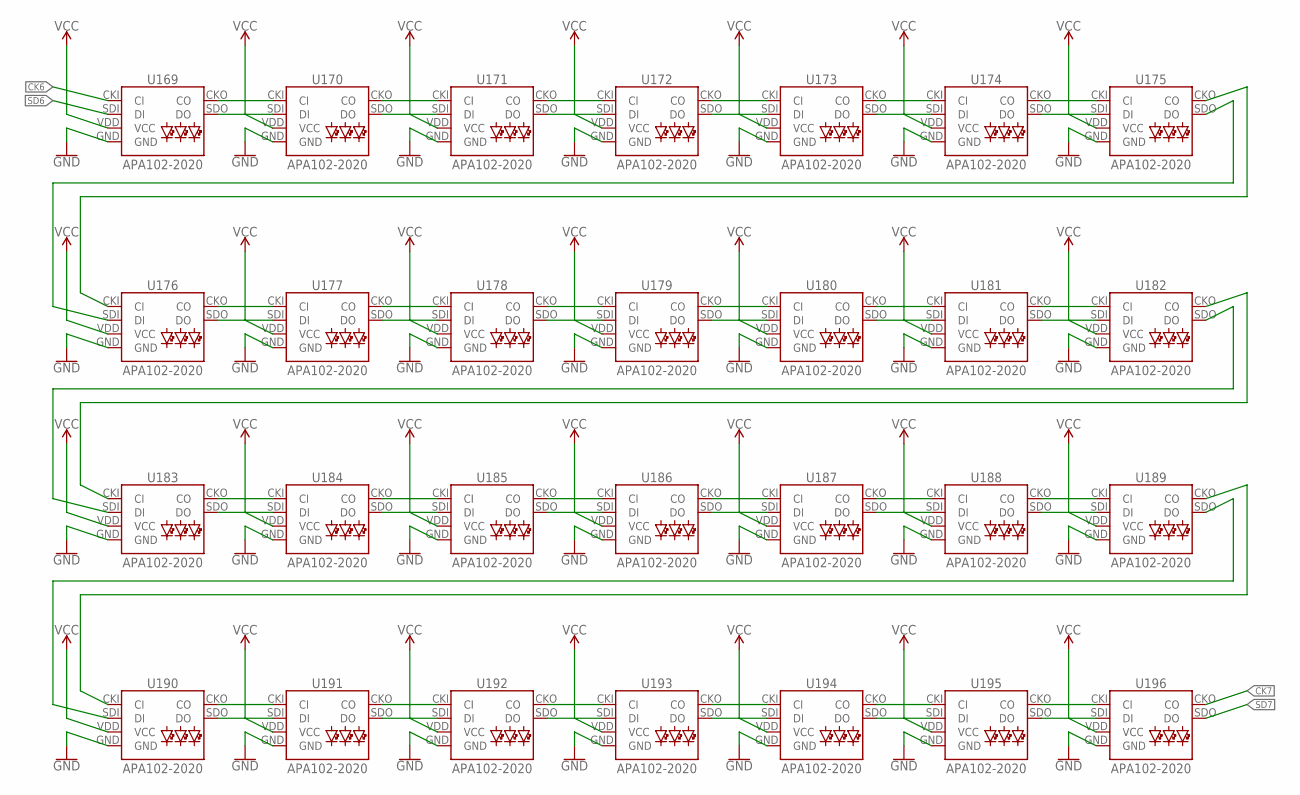
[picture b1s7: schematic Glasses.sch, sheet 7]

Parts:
U169, U170, U171, U172, U173, U174, U175, U176, U177, U178, U179, U180, U181, U182, U183, U184, U185, U186, U187, U188, U189, U190, U191, U192, U193, U194, U195, U196: APA102-2020

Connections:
CK6: U169.CKI (CI); also elsewhere on the board
CK7: U196.CKO (CO); also elsewhere on the board
GND: U169.GND, U170.GND, U171.GND, U172.GND, U173.GND, U174.GND, U175.GND, U176.GND, U177.GND, U178.GND, U179.GND, U180.GND, U181.GND, U182.GND, U183.GND, U184.GND, U185.GND, U186.GND, U187.GND, U188.GND, U189.GND, U190.GND, U191.GND, U192.GND, U193.GND, U194.GND, U195.GND, U196.GND; also elsewhere on the board
unnamed: U169.SDO (DO), U170.SDI (DI)
unnamed: U169.CKO (CO), U170.CKI (CI)
unnamed: U170.CKO (CO), U171.CKI (CI)
unnamed: U170.SDO (DO), U171.SDI (DI)
unnamed: U171.SDO (DO), U172.SDI (DI)
unnamed: U171.CKO (CO), U172.CKI (CI)
unnamed: U172.CKO (CO), U173.CKI (CI)
unnamed: U172.SDO (DO), U173.SDI (DI)
unnamed: U173.CKO (CO), U174.CKI (CI)
unnamed: U173.SDO (DO), U174.SDI (DI)
unnamed: U174.CKO (CO), U175.CKI (CI)
unnamed: U174.SDO (DO), U175.SDI (DI)
unnamed: U176.SDO (DO), U177.SDI (DI)
unnamed: U176.CKO (CO), U177.CKI (CI)
unnamed: U177.CKO (CO), U178.CKI (CI)
unnamed: U177.SDO (DO), U178.SDI (DI)
unnamed: U178.SDO (DO), U179.SDI (DI)
unnamed: U178.CKO (CO), U179.CKI (CI)
unnamed: U179.CKO (CO), U180.CKI (CI)
unnamed: U179.SDO (DO), U180.SDI (DI)
unnamed: U180.CKO (CO), U181.CKI (CI)
unnamed: U180.SDO (DO), U181.SDI (DI)
unnamed: U181.CKO (CO), U182.CKI (CI)
unnamed: U181.SDO (DO), U182.SDI (DI)
unnamed: U175.SDO (DO), U176.SDI (DI)
unnamed: U175.CKO (CO), U176.CKI (CI)
unnamed: U183.SDO (DO), U184.SDI (DI)
unnamed: U183.CKO (CO), U184.CKI (CI)
unnamed: U184.CKO (CO), U185.CKI (CI)
unnamed: U184.SDO (DO), U185.SDI (DI)
unnamed: U185.SDO (DO), U186.SDI (DI)
unnamed: U185.CKO (CO), U186.CKI (CI)
unnamed: U186.CKO (CO), U187.CKI (CI)
unnamed: U186.SDO (DO), U187.SDI (DI)
unnamed: U187.CKO (CO), U188.CKI (CI)
unnamed: U187.SDO (DO), U188.SDI (DI)
unnamed: U188.CKO (CO), U189.CKI (CI)
unnamed: U188.SDO (DO), U189.SDI (DI)
unnamed: U190.SDO (DO), U191.SDI (DI)
unnamed: U190.CKO (CO), U191.CKI (CI)
unnamed: U191.CKO (CO), U192.CKI (CI)
unnamed: U191.SDO (DO), U192.SDI (DI)
unnamed: U192.SDO (DO), U193.SDI (DI)
unnamed: U192.CKO (CO), U193.CKI (CI)
unnamed: U193.CKO (CO), U194.CKI (CI)
unnamed: U193.SDO (DO), U194.SDI (DI)
unnamed: U194.CKO (CO), U195.CKI (CI)
unnamed: U194.SDO (DO), U195.SDI (DI)
unnamed: U189.SDO (DO), U190.SDI (DI)
unnamed: U189.CKO (CO), U190.CKI (CI)
unnamed: U182.SDO (DO), U183.SDI (DI)
unnamed: U182.CKO (CO), U183.CKI (CI)
unnamed: U195.CKO (CO), U196.CKI (CI)
unnamed: U195.SDO (DO), U196.SDI (DI)
SD6: U169.SDI (DI); also elsewhere on the board
SD7: U196.SDO (DO); also elsewhere on the board
VCC: U169.VDD (VCC), U170.VDD (VCC), U171.VDD (VCC), U172.VDD (VCC), U173.VDD (VCC), U174.VDD (VCC), U175.VDD (VCC), U176.VDD (VCC), U177.VDD (VCC), U178.VDD (VCC), U179.VDD (VCC), U180.VDD (VCC), U181.VDD (VCC), U182.VDD (VCC), U183.VDD (VCC), U184.VDD (VCC), U185.VDD (VCC), U186.VDD (VCC), U187.VDD (VCC), U188.VDD (VCC), U189.VDD (VCC), U190.VDD (VCC), U191.VDD (VCC), U192.VDD (VCC), U193.VDD (VCC), U194.VDD (VCC), U195.VDD (VCC), U196.VDD (VCC); also elsewhere on the board

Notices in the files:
parts and their libraries:
SparkFun-Connectors: Licensing: Creative Commons ShareAlike 4.0 International - https://creativecommons.org/licenses/by-sa/4.0
SparkFun-Aesthetics: Released under the Creative Commons Attribution Share-Alike 4.0 License
SparkFun-Aesthetics: https://creativecommons.org/licenses/by-sa/4.0
